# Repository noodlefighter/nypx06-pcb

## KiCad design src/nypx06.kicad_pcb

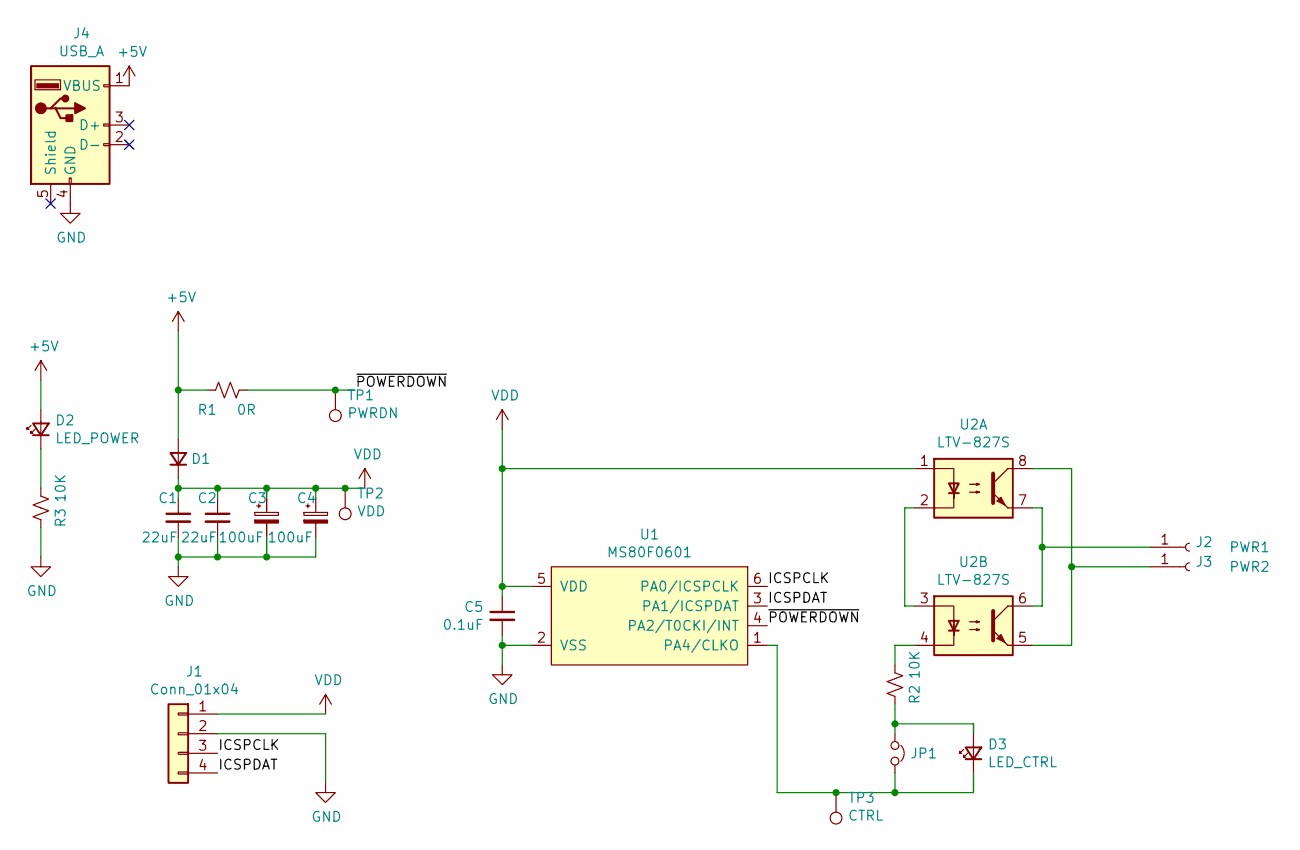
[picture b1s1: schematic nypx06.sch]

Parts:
C1, C2: 22uF; C_0805_2012Metric_Pad1.18x1.45mm_HandSolder
C3, C4: 100uF; CP_Elec_5x5.4
C5: 0.1uF; C_0603_1608Metric_Pad1.08x0.95mm_HandSolder
D1: D_Small; D_0603_1608Metric_Pad1.05x0.95mm_HandSolder
D2: LED_POWER; LED_0603_1608Metric_Pad1.05x0.95mm_HandSolder
D3: LED_CTRL; LED_0603_1608Metric_Pad1.05x0.95mm_HandSolder
J1: Conn_01x04; PinHeader_1x04_P2.54mm_Horizontal
J2: PWR1; SolderWirePad_1x01_SMD_1x2mm
J3: PWR2; SolderWirePad_1x01_SMD_1x2mm
J4: USB_A; USB_A_CNCTech_1001-011-01101_Horizontal
JP1: Jumper_NC_Small; SolderJumper-2_P1.3mm_Bridged_RoundedPad1.0x1.5mm
R1: 0R; R_0603_1608Metric
R2, R3: 10K; R_0603_1608Metric
TP1: PWRDN; TestPoint_Pad_D1.5mm
TP2: VDD; TestPoint_Pad_D1.5mm
TP3: CTRL; TestPoint_Pad_D1.5mm
U1: MS80F0601; SOT-23-6
U2: LTV-827S; SMDIP-8_W9.53mm

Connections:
+5V: D1.2 (A), D2.2 (A), J4.1 (VBUS), R1.1
/ICSPCLK: J1.3, U1.6 (PA0/ICSPCLK)
/ICSPDAT: J1.4, U1.3 (PA1/ICSPDAT)
/~POWERDOWN: R1.2, TP1.1, U1.4 (PA2/T0CKI/INT)
GND: C1.2, C2.2, C3.2, C4.2, C5.2, J1.2, J4.4 (GND), R3.2, U1.2 (VSS)
unnamed: D2.1 (K), R3.1
unnamed: D3.1 (K), JP1.2, TP3.1, U1.1 (PA4/CLKO)
unnamed: D3.2 (A), JP1.1, R2.2
unnamed: J2.1, U2.6, U2.7
unnamed: J3.1, U2.5, U2.8
unnamed: R2.1, U2.4
unnamed: U2.2, U2.3
VDD: C1.1, C2.1, C3.1, C4.1, C5.1, D1.1 (K), J1.1, TP2.1, U1.5 (VDD), U2.1

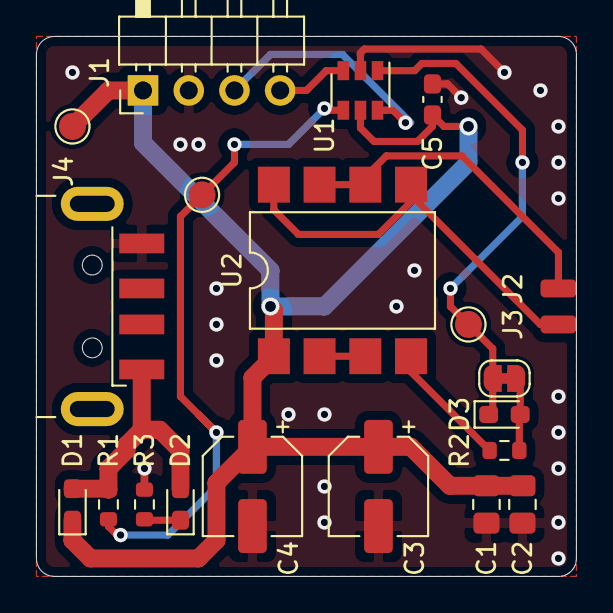
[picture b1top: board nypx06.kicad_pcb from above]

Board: 2 copper layers, 30.0 x 30.0 mm, 21 parts (0 on the bottom side), 13 nets.

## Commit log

2021-09-08 init
